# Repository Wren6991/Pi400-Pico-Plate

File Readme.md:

Pi 400 Pico Plate
=================

This board connects a Pico to the GPIO header on a Pi 400, without any wires flapping in the breeze. [See the schematic here (PDF)](pi400-pico-plate.pdf).

I made this to use at work. Besides connecting power and debug, it clearly labels the Pico pinout when viewed from the top:

- Pico VSYS is powered from Pi +5V rail
- Pico SWD is connected to Pi GPIO 24/25
- Pico RUN pin is connected to a push-button
- *(jumper)* Pico UART on GPIO0/1 is connected to Pi GPIO14/15
- *(jumper)* Pico VBUS is powered from +5V rail so Pico can function as USB host

That's it, that's the whole thing. This repository is CC0-licensed, with the exception of the 3d models in the `3d/` directory.

The board is designed with KiCad nightly; if you don't have KiCad nightly installed, you can find pregenerated gerbers of the rev A PCB in the `gerb/` directory, which are suitable for manufacture by JLCPCB.

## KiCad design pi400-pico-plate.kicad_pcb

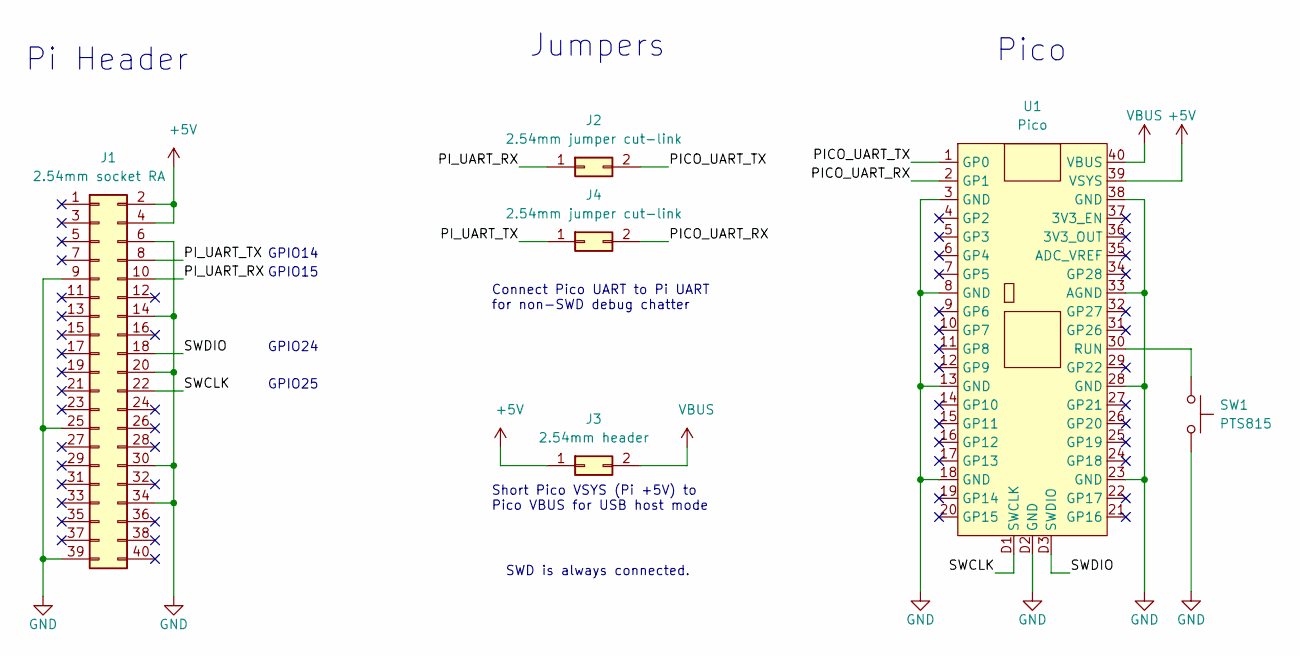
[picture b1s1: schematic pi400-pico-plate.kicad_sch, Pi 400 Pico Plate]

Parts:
J1: 2.54mm socket RA; PinSocket_2x20_P2.54mm_Horizontal
J2, J4: 2.54mm jumper cut-link; 2.54mm- jumper-closed
J3: 2.54mm header; PinHeader_2x01_P2.54mm_Vertical
SW1: PTS815; SW_SPST_PTS815
U1: Pico

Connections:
+5V: J1.2, J1.4, J3.1, U1.39 (VSYS)
/PICO_UART_RX: J4.2, U1.2 (GP1)
/PICO_UART_TX: J2.2, U1.1 (GP0)
/PI_UART_RX: J1.10, J2.1
/PI_UART_TX: J1.8, J4.1
/SWCLK: J1.22, U1.D1 (SWCLK)
/SWDIO: J1.18, U1.D3 (SWDIO)
GND: J1.6, J1.9, J1.14, J1.20, J1.25, J1.30, J1.34, J1.39, SW1.2, U1.3 (GND), U1.8 (GND), U1.13 (GND), U1.18 (GND), U1.23 (GND), U1.28 (GND), U1.33 (AGND), U1.38 (GND), U1.D2 (GND)
unnamed: SW1.1, U1.30 (RUN)
VBUS: J3.2, U1.40 (VBUS)

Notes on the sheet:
Pi Header
GPIO14
GPIO15
GPIO24
GPIO25
Connect Pico UART to Pi UART for non-SWD debug chatter
Short Pico VSYS (Pi +5V) to Pico VBUS for USB host mode
SWD is always connected.
Jumpers
Pico

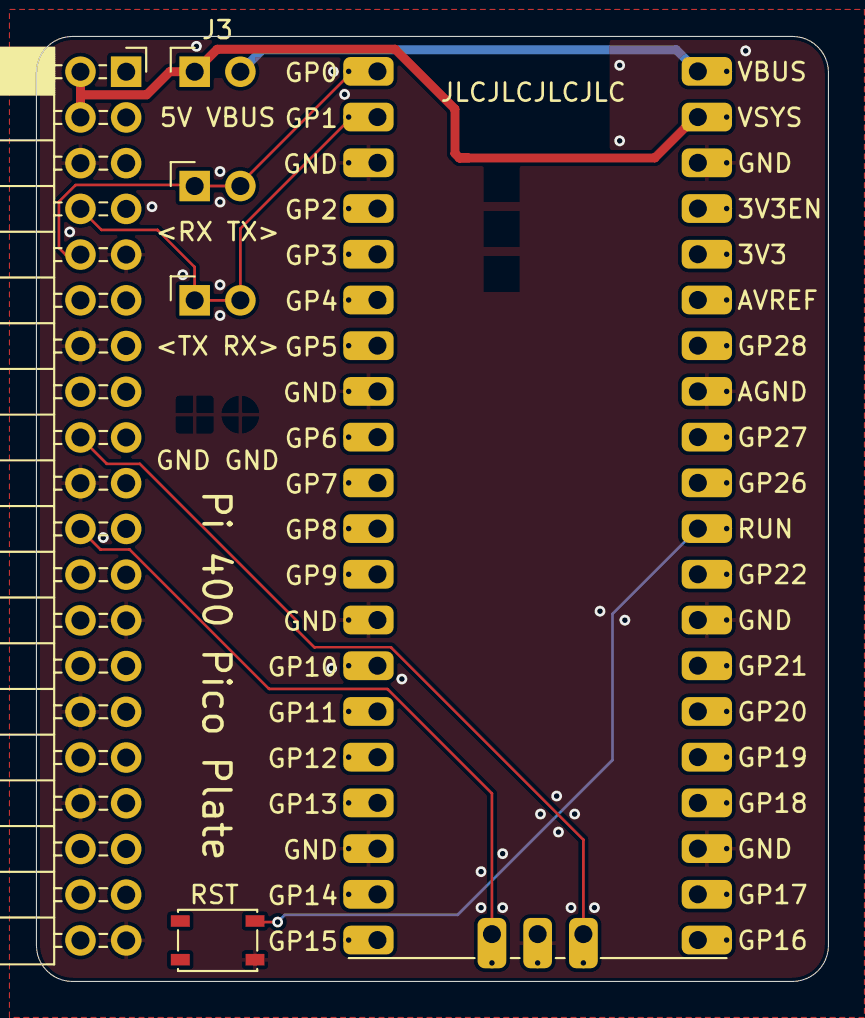
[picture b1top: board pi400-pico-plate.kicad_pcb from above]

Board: 2 copper layers, 44.0 x 52.5 mm, 6 parts (0 on the bottom side), 10 nets.

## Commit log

2021-03-06 Initial commit (rev A)
2021-03-06 Add readme and images
2021-03-06 Create LICENSE
2021-03-08 Add indicator LEDs, trim bottom board edge by 0.5 mm (by Pico SWD pads)
2021-03-08 Add mounting holes for standoffs. Power layout changed as a result
2021-03-08 Start rev B changes -- make UART jumpers cut-link, remove aux GND header
